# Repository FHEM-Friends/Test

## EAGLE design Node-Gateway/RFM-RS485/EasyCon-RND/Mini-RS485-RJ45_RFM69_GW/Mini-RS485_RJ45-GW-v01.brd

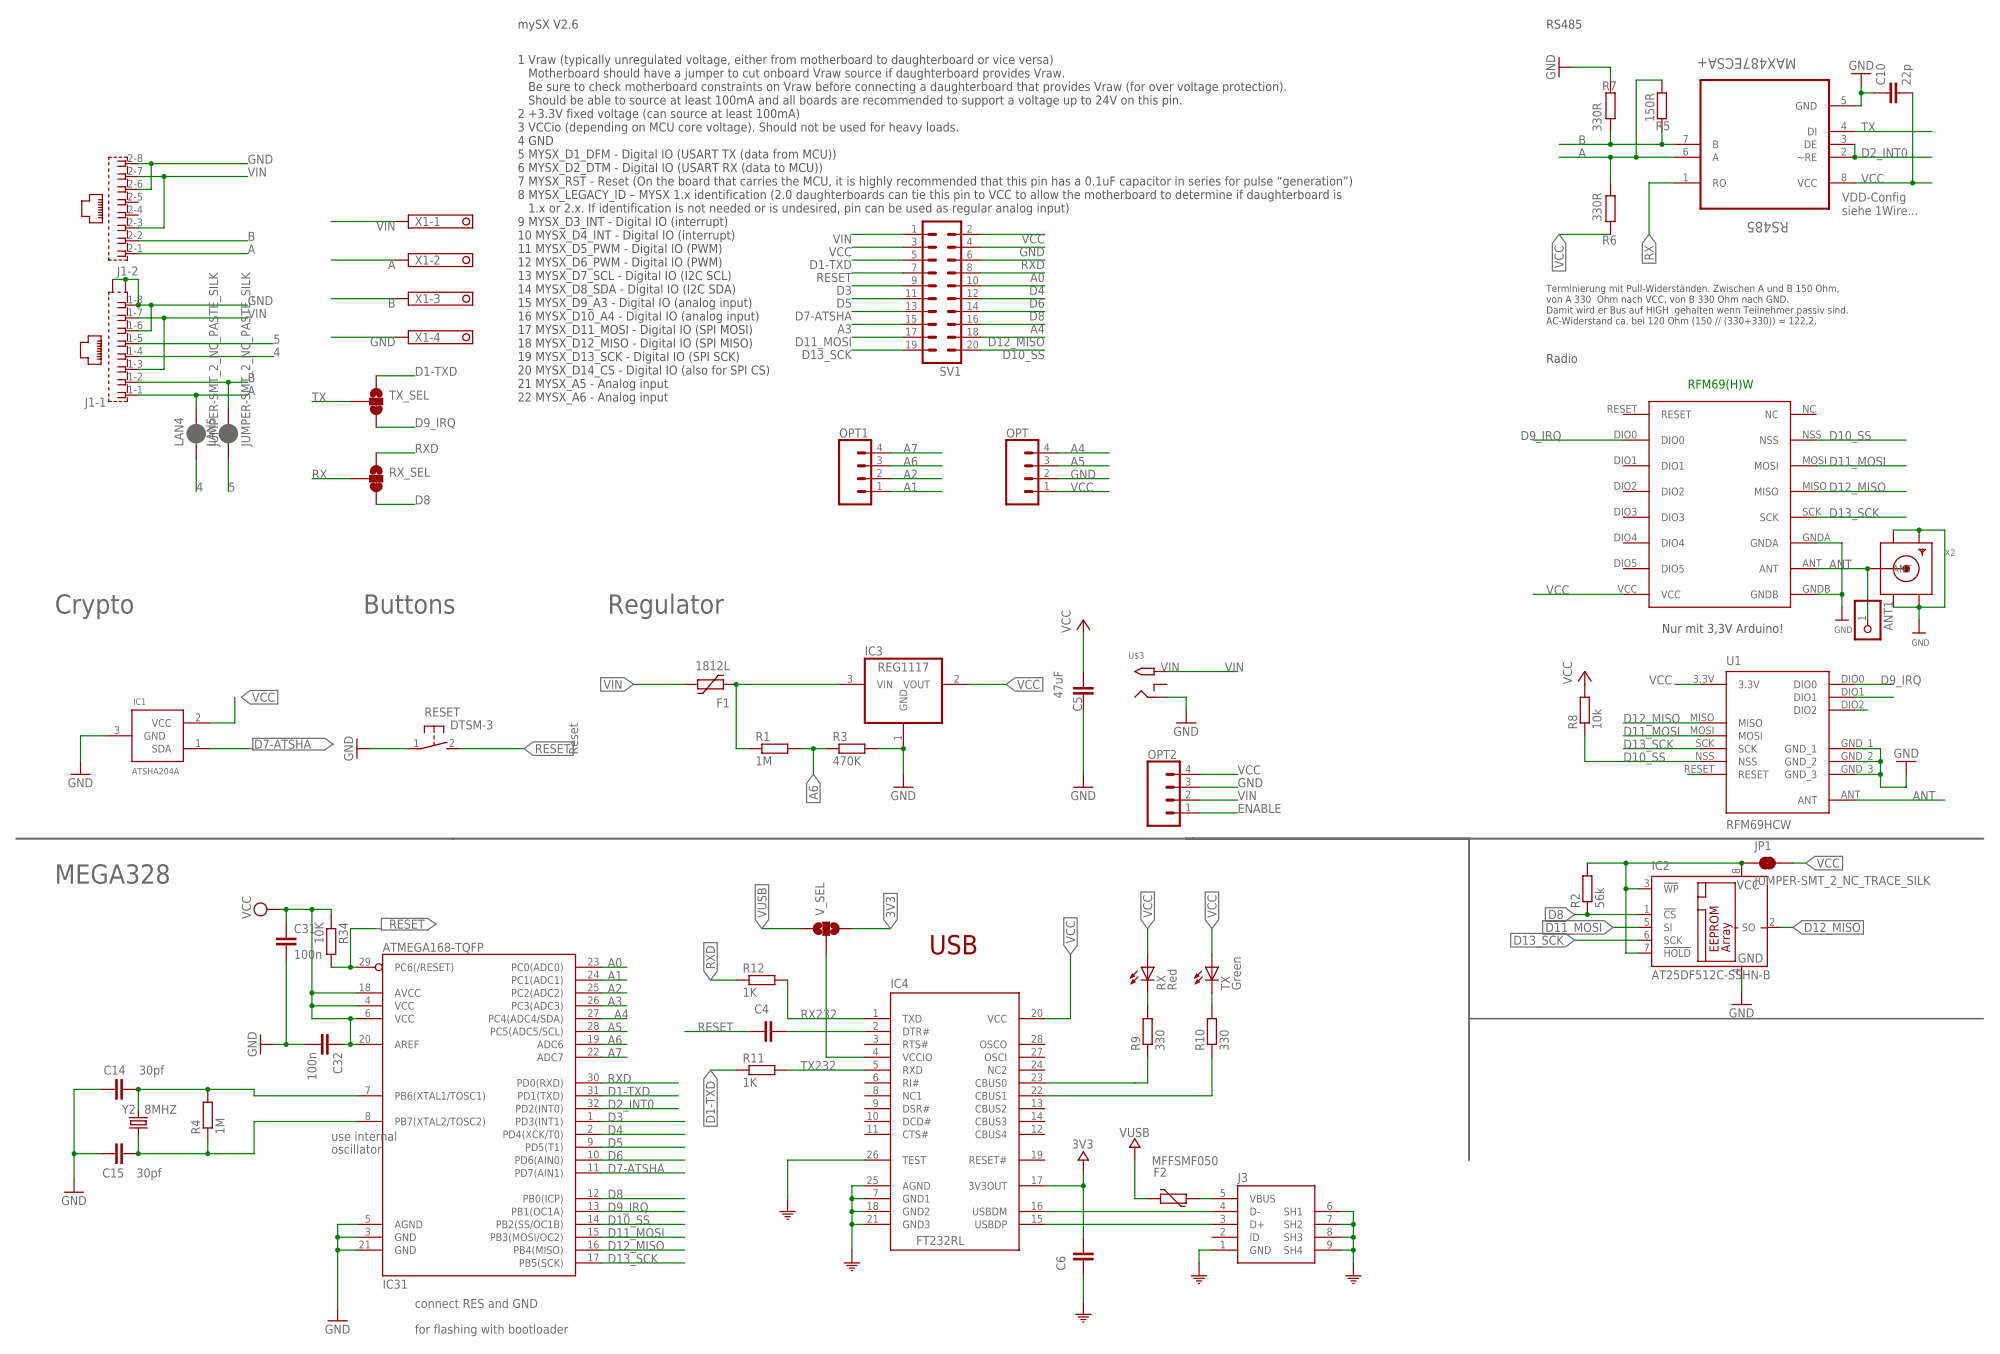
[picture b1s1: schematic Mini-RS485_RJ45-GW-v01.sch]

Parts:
ANT1: PINHD-1X1; 1X01
C4, C6: 100nF; C0805
C5: 47uF; C1210
C10: 22p; C0805
C14, C15: 30pf; 0805
C31, C32: 100n; C0805
F1: 1812L
F2: MFFSMF050; 0603-1608X90N
IC1: ATSHA204A; SOT23
IC2: AT25DF512C-SSHN-B; SO-08
IC3: REG1117; SOT223
IC4: FT232RL; SSOP28
IC31: ATMEGA168-TQFP; TQFP32-08
J1: RJ45_2X_NARROW_SHILDPINS
J3: 0219_14850; USB-MINI-B_2
JP1: JUMPER-SMT_2_NC_TRACE_SILK; SMT-JUMPER_2_NC_TRACE_SILK
LAN4, LAN5: JUMPER-SMT_2_NC_PASTE_SILK; SMT-JUMPER_2_NC_PASTE_SILK
OPT, OPT1, OPT2: CONN_04; 1X04
R1, R4: 1M; M0805
R2: 56k; M0805
R3: 470K; R0805
R5: 150R; R0805
R6, R7: 330R; R0805
R8: 10k; M0805
R9, R10: 330; R0805
R11, R12: 1K; R0805
R34: 10K; R0805
RESET: DTSM-3
RFM69W: RFM69HW; RFM
RS485: MAX487ECSA+; SOIC127P600X175-8N
RX: Red; CHIPLED_0805
RX_SEL: JUMPER-SMT_3_1-NC_TRACE_SILK; SMT-JUMPER_3_1-NC_TRACE_SILK
SV1: MA10-2
TX: Green; CHIPLED_0805
TX_SEL: JUMPER-SMT_3_1-NC_TRACE_SILK; SMT-JUMPER_3_1-NC_TRACE_SILK
U1: RFM69HCW; RFM69HCW-XXXS2
U$3: 2.1MMJACKTHM; PJ-102A
V_SEL: JUMPER-SMT_3_NO_SILK; SMT-JUMPER_3_NO_SILK
X1: 1751264
X2: SMACONNECTOR_EDGE; SMA_EDGELAUNCH
Y2: 8MHZ; CRYSTAL-TXC-7A

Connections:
3V3: C6.2, IC4.17 (3V3OUT), V_SEL.3
4: J1.1-4 (4), LAN4.1
5: J1.1-5 (5), LAN5.1
A: J1.1-1 (1), J1.2-1 (1), LAN4.2, R5.1, R6.2, RS485.6 (A), X1.2
A0: IC31.23 (PC0(ADC0)), SV1.8
A1: IC31.24 (PC1(ADC1)), OPT1.1
A2: IC31.25 (PC2(ADC2)), OPT1.2
A3: IC31.26 (PC3(ADC3)), SV1.15
A4: IC31.27 (PC4(ADC4/SDA)), OPT.4, SV1.16
A5: IC31.28 (PC5(ADC5/SCL)), OPT.3
A6: IC31.19 (ADC6), OPT1.3, R1.2, R3.1
A7: IC31.22 (ADC7), OPT1.4
ANT: ANT1.1, RFM69W.ANT, U1.ANT, X2.P (ANT)
B: J1.1-2 (2), J1.2-2 (2), LAN5.2, R5.2, R7.1, RS485.7 (B), X1.3
COM: C6.1, IC4.7 (GND1), IC4.18 (GND2), IC4.21 (GND3), IC4.25 (AGND), IC4.26 (TEST), J3.1 (GND), J3.6 (SH1), J3.7 (SH2), J3.8 (SH3), J3.9 (SH4)
D1-TXD: IC31.31 (PD1(TXD)), R11.1, SV1.5, TX_SEL.1
D2_INT0: IC31.32 (PD2(INT0)), RS485.2 (~RE), RS485.3 (DE)
D3: IC31.1 (PD3(INT1)), SV1.9
D4: IC31.2 (PD4(XCK/T0)), SV1.10
D5: IC31.9 (PD5(T1)), SV1.11
D6: IC31.10 (PD6(AIN0)), SV1.12
D7-ATSHA: IC1.1 (SDA), IC31.11 (PD7(AIN1)), SV1.13
D8: IC2.1 (!CS), IC31.12 (PB0(ICP)), R2.1, RX_SEL.3, SV1.14
D9_IRQ: IC31.13 (PB1(OC1A)), RFM69W.DIO0, TX_SEL.3, U1.DIO0
D10_SS: IC31.14 (PB2(SS/OC1B)), R8.1, RFM69W.NSS, SV1.20, U1.NSS
D11_MOSI: IC2.5 (SI), IC31.15 (PB3(MOSI/OC2)), RFM69W.MOSI, SV1.17, U1.MOSI
D12_MISO: IC2.2 (SO), IC31.16 (PB4(MISO)), RFM69W.MISO, SV1.18, U1.MISO
D13_SCK: IC2.6 (SCK), IC31.17 (PB5(SCK)), RFM69W.SCK, SV1.19, U1.SCK
ENABLE: OPT2.1
GND: C5.1, C10.1, C14.1, C15.1, C31.2, C32.2, IC1.3 (GND), IC2.4 (GND), IC3.1 (GND), IC31.3 (GND), IC31.5 (AGND), IC31.21 (GND), J1.1-6 (6), J1.1-8 (8), J1.2-6 (6), J1.2-8 (8), J1.G1 (S1), J1.G3 (S2), OPT.2, OPT2.3, R3.2, R7.2, RESET.1, RFM69W.GNDA, RFM69W.GNDB, RS485.5 (GND), SV1.4, U1.GND_1, U1.GND_2, U1.GND_3, U$3.RING, X1.4, X2.GND@1 (GND4), X2.GND@2 (GND3), X2.GND@3 (GND2), X2.GND@4 (GND1)
unnamed: IC4.4 (VCCIO), V_SEL.2
unnamed: IC4.22 (CBUS1), R10.1
unnamed: C14.2, IC31.7 (PB6(XTAL1/TOSC1)), R4.2, Y2.P$2 (2)
unnamed: C4.2, IC4.2 (DTR#)
unnamed: IC4.15 (USBDP), J3.3 (D+)
unnamed: IC4.16 (USBDM), J3.4 (D-)
unnamed: R9.2, RX.C
unnamed: IC4.23 (CBUS0), R9.1
unnamed: R10.2, TX.C
unnamed: C15.2, IC31.8 (PB7(XTAL2/TOSC2)), R4.1, Y2.P$1 (1)
unnamed: F2.2, J3.5 (VBUS)
RESET: C4.1, IC31.29 (PC6(/RESET)), R34.2, RESET.2, SV1.7
RX: RS485.1 (RO), RX_SEL.2
RX232: IC4.1 (TXD), R12.2
RXD: IC31.30 (PD0(RXD)), R12.1, RX_SEL.1, SV1.6
TX: RS485.4 (DI), TX_SEL.2
TX232: IC4.5 (RXD), R11.2
VCC: C5.2, C10.2, C31.1, C32.1, IC1.2 (VCC), IC3.2 (VOUT), IC4.20 (VCC), IC31.4 (VCC), IC31.6 (VCC), IC31.18 (AVCC), IC31.20 (AREF), JP1.2, OPT.1, OPT2.4, R6.1, R8.2, R34.1, RFM69W.VCC, RS485.8 (VCC), RX.A, SV1.2, SV1.3, TX.A, U1.3.3V
VCC1: IC2.3 (!WP), IC2.7 (!HOLD), IC2.8 (VCC), JP1.1, R2.2
VIN: F1.P$2 (2), J1.1-3 (3), J1.1-7 (7), J1.2-3 (3), J1.2-7 (7), OPT2.2, SV1.1, U$3.TIP, X1.1
VIN-FUSED: F1.P$1 (1), IC3.3 (VIN), R1.1
VUSB: F2.1, V_SEL.1

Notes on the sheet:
MEGA328
use internal
oscillator
connect RES and GND
for flashing with bootloader
Reset
Crypto
Buttons
Regulator
RS485
VDD-Config siehe 1Wire...
Terminierung mit Pull-Widerständen. Zwischen A und B 150 Ohm, von A 330 Ohm nach VCC, von B 330 Ohm nach GND. Damit wird er Bus auf HIGH gehalten wenn Teilnehmer passiv sind. AC-Widerstand ca. bei 120 Ohm (150 // (330+330)) = 122,2.
1 Vraw (typically unregulated voltage, either from motherboard to daughterboard or vice versa) Motherboard should have a jumper to cut onboard Vraw source if daughterboard provides Vraw. Be sure to check motherboard constraints on Vraw before connecting a daughterboard that provides Vraw (for over 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
mySX V2.6
RFM69(H)W
Nur mit 3,3V Arduino!
Radio
USB

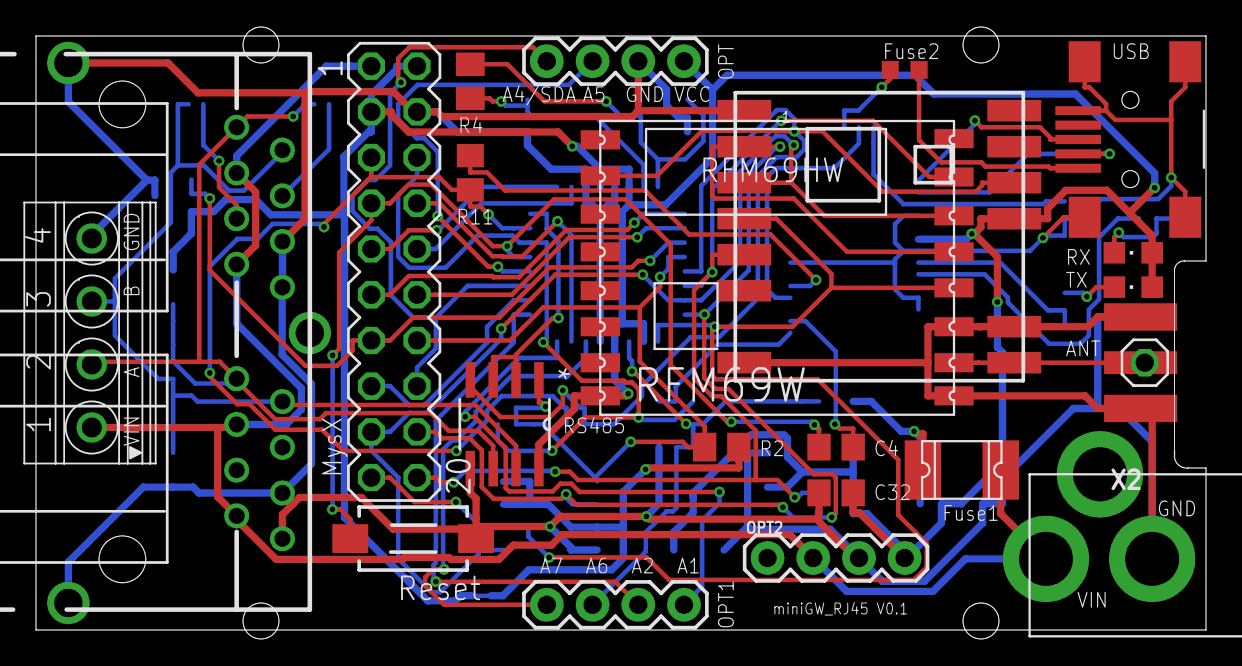
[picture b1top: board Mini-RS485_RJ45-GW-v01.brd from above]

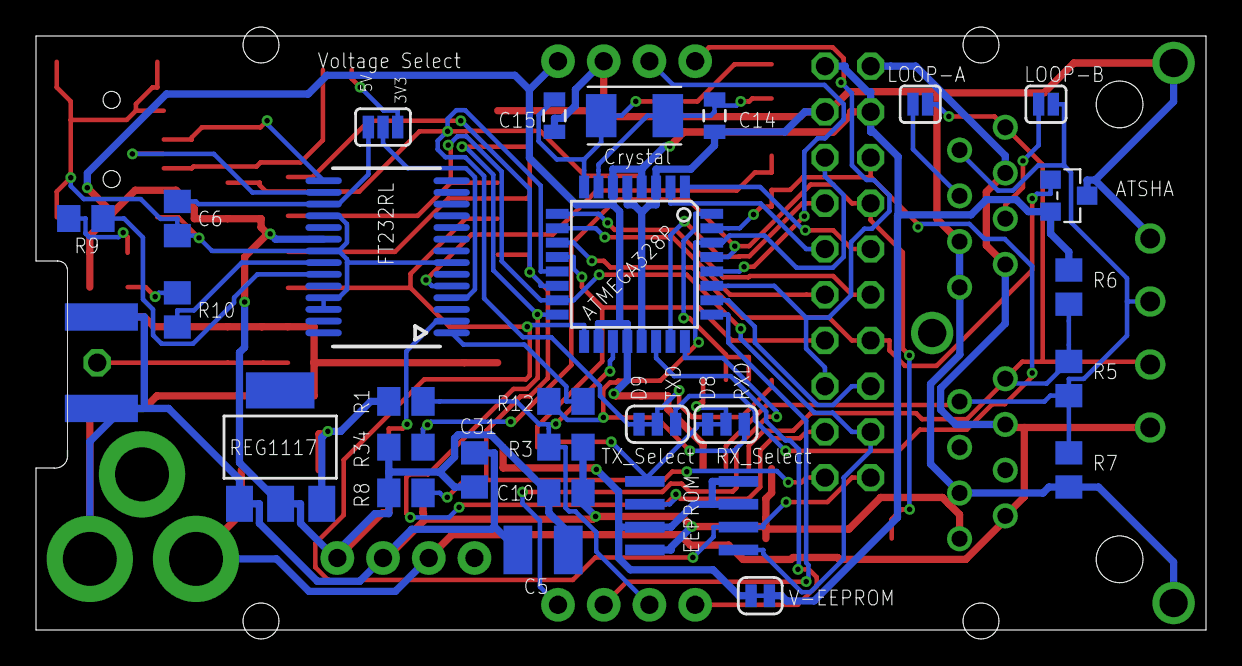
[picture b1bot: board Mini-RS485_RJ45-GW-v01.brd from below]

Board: 2 copper layers, 65.0 x 33.0 mm, 51 parts (28 on the bottom side), 51 nets.

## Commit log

2018-03-01 RND_455-00307-easySens-RS485
2018-03-01 readme
2018-03-01 Addon + Sensor
2018-03-01 Restructure
2018-03-01 test2
2018-03-01 RS485-RJ45/RFM GW V0.1
    RS485-RJ45/RFM Gateway/Node for RND Case V0.1
2018-03-01 RS485-RJ45/RFM GW V0.1
2018-03-01 V003
    Vorschlag ;)
2018-03-01 Anschluss Regler geaendert
2018-03-01 gelöscht
2018-03-01 Mini-RS485-RJ45_RFM69_GW added
2018-03-02 easySens
2018-03-02 Pfad aktualisiert

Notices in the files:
parts and their libraries:
SparkFun-FreqCtrl: Licensing: Creative Commons ShareAlike 4.0 International - https://creativecommons.org/licenses/by-sa/4.0
Arduino-rcl: Copyright (c) 2016-2017 Arduino LLC.  All right reserved.
